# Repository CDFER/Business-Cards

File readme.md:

# PCB Business Cards

Welcome to my PCB business cards, a collection of functional devices showcasing my passion for embedded electronics and microcontrollers. Each card is a unique project demonstrating a specific concept or technology.

## USB Cable Tester MK2

* Simple, battery-powered USB 2.0 and 3.0 cable tester
* Protected by Schottky diodes and a polyfuse
* Indicates test results with LEDs

[Project Page](https://github.com/CDFER/Business-Cards/tree/main/USB_Cable_Tester_MK2)

## Tea Cozy Hotplate

* Temperature-controlled hotplate for perfect tea temperature
* Compact design, precise temperature control, and user-friendly interface

[Project Page](https://github.com/CDFER/Business-Cards/tree/main/Tea_Cozy_Hotplate)

## USB MicroPad

* 8-button macro pad for productivity shortcuts and macros
* Implemented as a USB HID keyboard and HID media consumer controller

[Project Page](https://github.com/CDFER/Business-Cards/tree/main/USB_Keypad)

## WLED Matrix

* 7x9 RGB matrix display powered by an ESP32C3 microcontroller
* Controlled from any web browser using WLED firmware

[Project Page](https://github.com/CDFER/Business-Cards/tree/main/WLED_Matrix)

## USB Cable Tester MK1

* Simple, battery-powered USB 2.0 and 3.0 cable tester
* Protected by Schottky diodes and a polyfuse
* Indicates test results with 0603 green LEDs

[Project Page](https://github.com/CDFER/Business-Cards/tree/main/USB_Cable_Tester)

### Support

Support my work by purchasing a custom CO2 sensor on my website or hiring me for freelance Embedded Electronics projects: [https://www.keastudios.co.nz](https://www.keastudios.co.nz/about.htm).

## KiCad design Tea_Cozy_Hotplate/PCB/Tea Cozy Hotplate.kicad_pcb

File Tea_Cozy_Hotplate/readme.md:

**Tea Cozy Hotplate**
=====================================

### Overview

The Tea Cozy Hotplate is a temperature-controlled hotplate designed to keep your cup of tea at the perfect temperature. It features a compact design, precise temperature control, and a user-friendly interface.

### Features

* Temperature control with ±2°C accuracy
* Compact design fits most tea cups
* User-friendly interface with addressable LED indicators
* Powered via USB-C connector (5V, 1.4A)
* STM32F103C8T6 microcontroller with 72MHz CPU

### Specifications

#### STM32 Specifications

* **CPU**: Arm Cortex-M3 @ 72MHz
* **Flash**: 64KB
* **RAM**: 20KB
* **Package**: LQFP-48

#### Components

* **Microcontroller**: STM32F103C8T6
* **LDO Regulator**: XC6206P332MR
* **ESD Protection**: SRV05
* **Fuse**: 2 x 1.5A Resettable Fuses
* **USB Connector**: USB-C Receptacle
* **Heating Element**: ~3.75Ω Spiral PCB Coil
* **Temperature Sensor**: 47kΩ NTC Thermistor

### Assembly and Programming

* Program the STM32 microcontroller using an ST-Link V2

### Issues with V1

* 3V3 LDO pinout incorrect

### Improvements for V2

* Reduce 3V3 LED brightness (half brightness)
* Use a cheaper USB-C connector
* Lower Resistance PCB Coil
* Consider Multi-Zone Heater
* Remove reset button?

## JLCPCB Heater Coil (1mm PCB with 1oz/ft^2)

* **Trace**: 2.8m length, 0.55mm width, 1oz/ft^2
* **Calculated Resistance**: 2.47Ω (assuming 0.000017Ω.mm)
* **Real-World Resistance**: 3.75Ω (calculated to be 0.0000258Ω.mm)

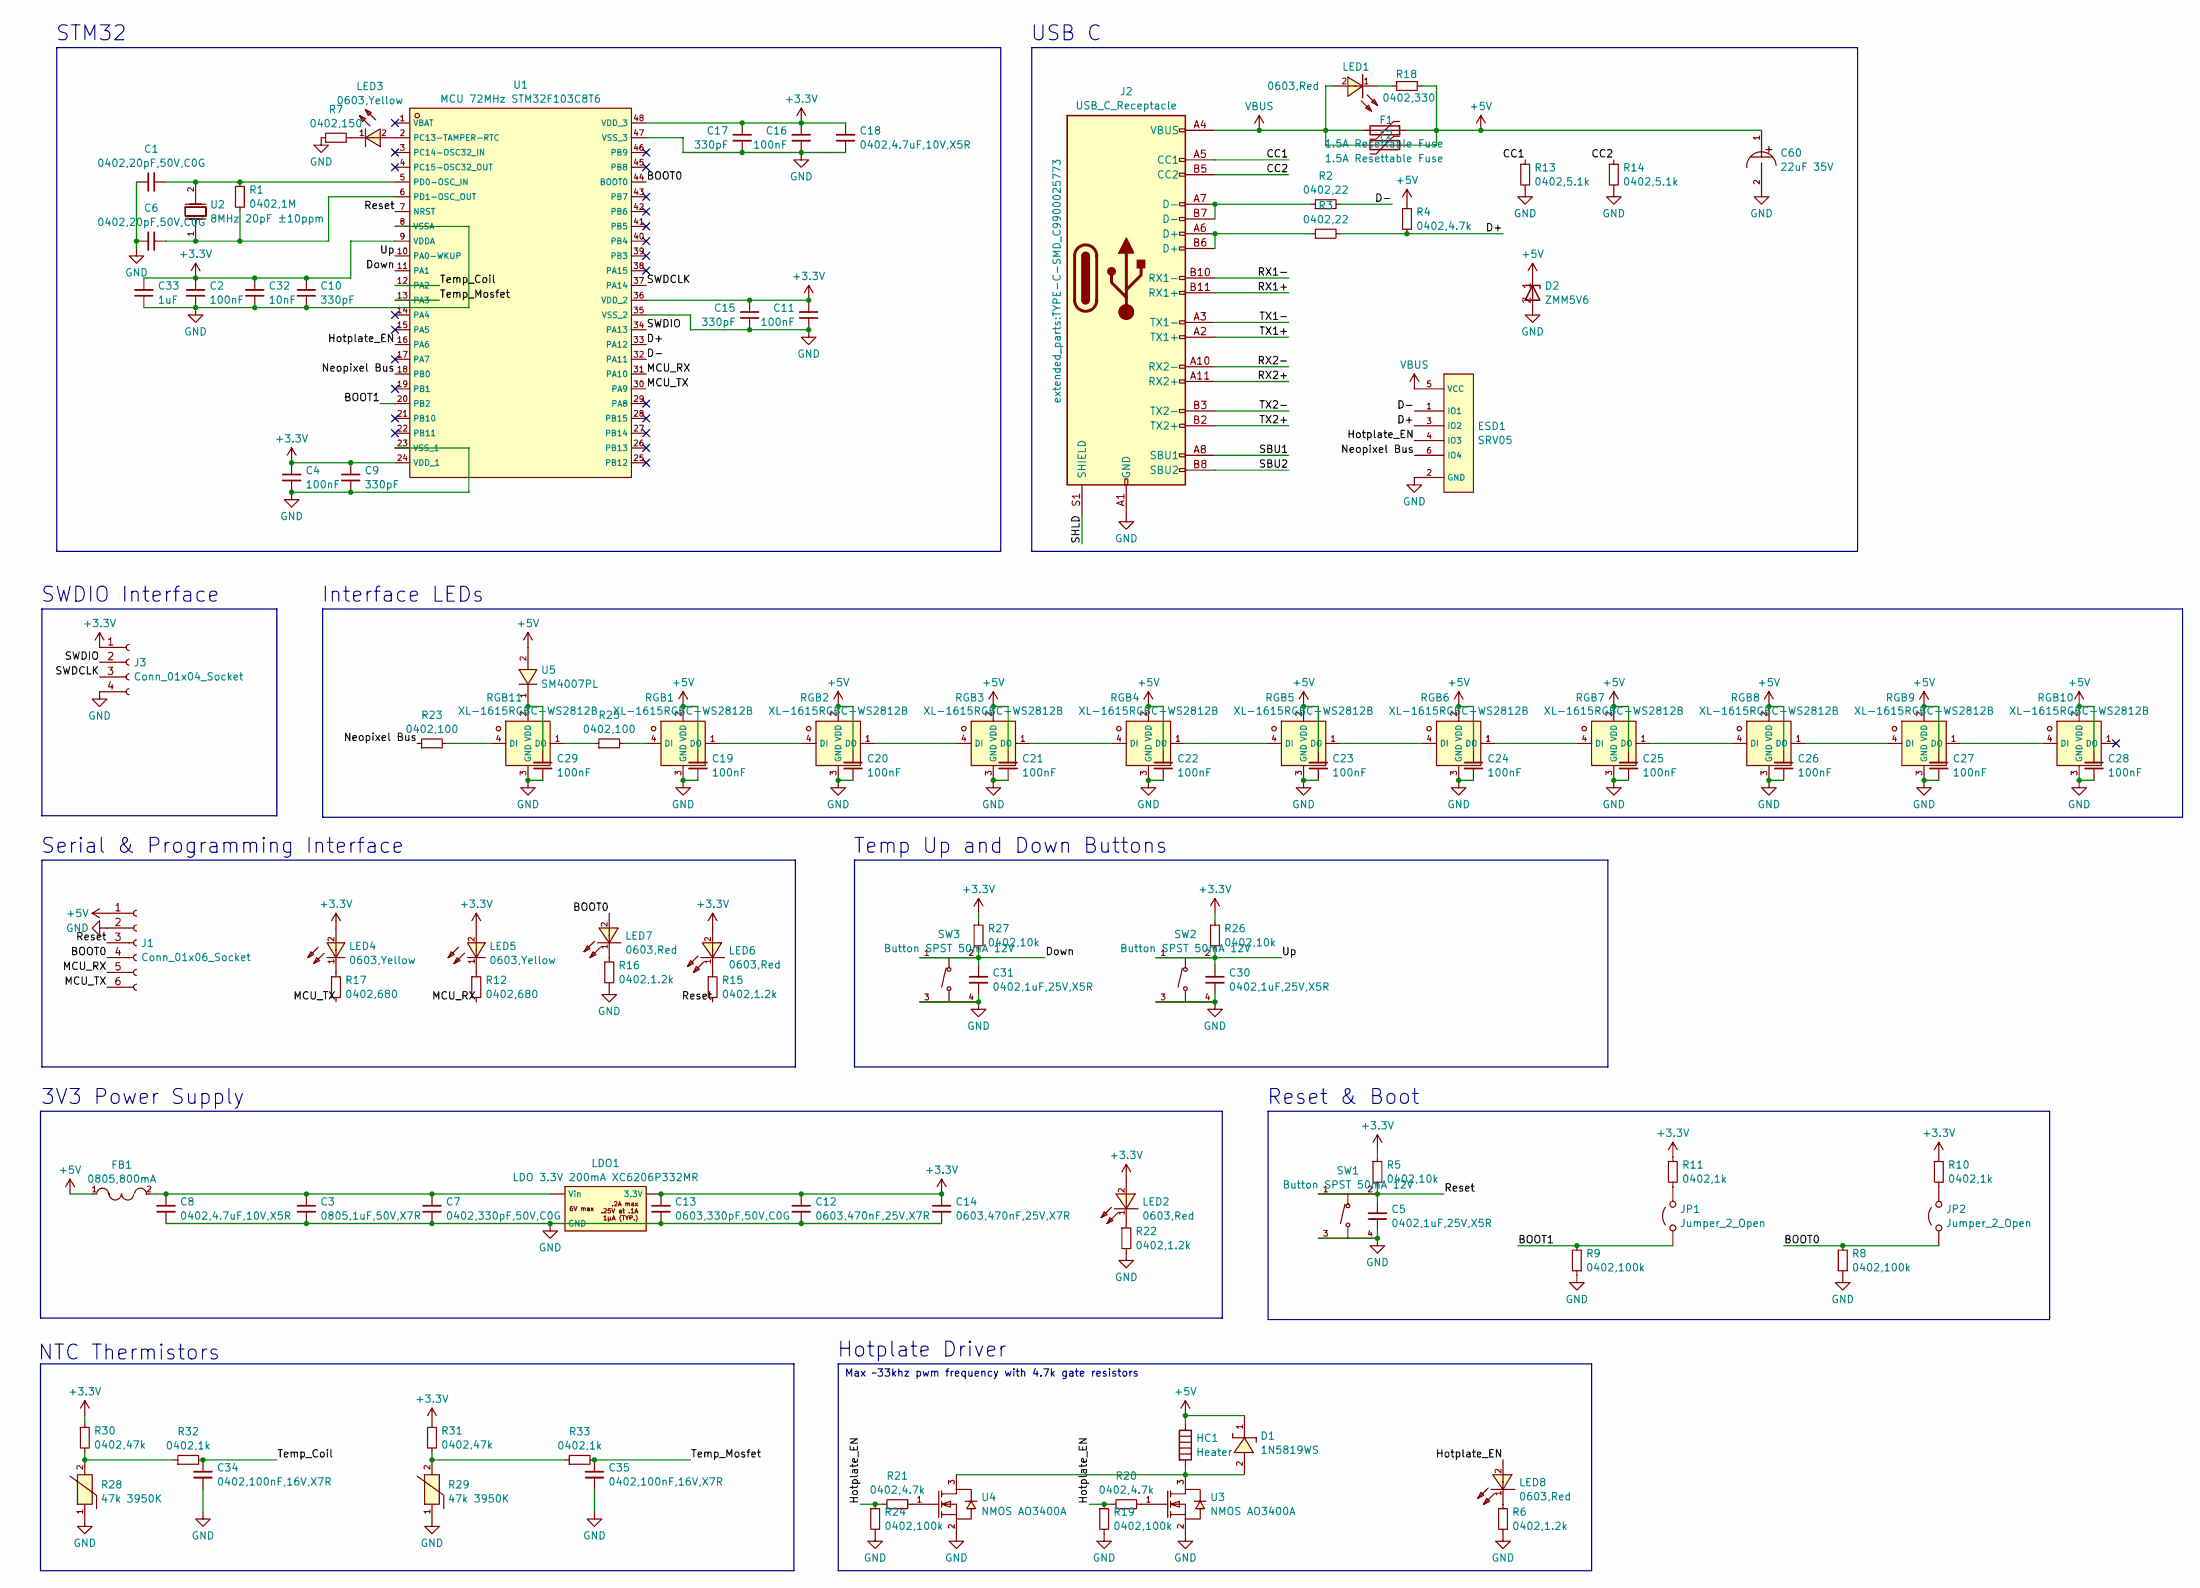
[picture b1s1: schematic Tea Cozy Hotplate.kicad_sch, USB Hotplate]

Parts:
C1, C6: 0402,20pF,50V,C0G; 0402_1005Metric; MFGPN 0402CG200J500NT; LCSC C1554
C2, C4, C11, C16, C19, C20, C21, C22, C23, C24, C25, C26, C27, C28, C29: 100nF; 0402_1005Metric; MFGPN CL05B104KO5NNNC; LCSC C1525
C3: 0805,1uF,50V,X7R; 0805_2012Metric; MFGPN CL21B105KBFNNNE; LCSC C28323
C5, C30, C31: 0402,1uF,25V,X5R; 0402_1005Metric; MFGPN CL05A105KA5NQNC; LCSC C52923
C7: 0402,330pF,50V,C0G; 0402_1005Metric; MFGPN CL05C331JB5NNNC; LCSC C13533
C8, C18: 0402,4.7uF,10V,X5R; 0402_1005Metric; MFGPN CL05A475MP5NRNC; LCSC C23733
C9, C10, C15, C17: 330pF; 0402_1005Metric; MFGPN CL05C331JB5NNNC; LCSC C13533
C12, C14: 0603,470nF,25V,X7R; 0603_1608Metric; MFGPN CL10B474KA8NNNC; LCSC C1623
C13: 0603,330pF,50V,C0G; 0603_1608Metric; MFGPN CL10C331JB8NNNC; LCSC C1664
C32: 10nF; 0402_1005Metric; MFGPN CL05B103KB5NNNC; LCSC C15195
C33: 1uF; 0805_2012Metric; MFGPN CL21B105KBFNNNE; LCSC C28323
C34, C35: 0402,100nF,16V,X7R; 0402_1005Metric; MFGPN CL05B104KO5NNNC; LCSC C1525
C60: 22uF 35V; CAP-SMD_BD5.0-L5.3-W5.3-LS6.0-FD; LCSC C2887274
D1: 1N5819WS; SOD-323_L1.8-W1.3-LS2.5-RD; LCSC C191023
D2: ZMM5V6; LL-34_L3.5-W1.5-RD; LCSC C8062
ESD1: SRV05; SOT-23-6_L2.9-W1.6-P0.95-LS2.8-BR; LCSC C85364
F1, F2: 1.5A Resettable Fuse; Fuse_1206_3216Metric; LCSC C2838983
FB1: 0805,800mA; 0805_2012Metric; LCSC C1015
HC1: Heater; heater_coil
J1: Conn_01x06_Socket; PinHeader_1x06_P2.54mm_Vertical
J2: USB_C_Receptacle; TYPE-C-SMD_C9900025773; LCSC C5156605
J3: Conn_01x04_Socket; PinHeader_1x04_P2.54mm_Vertical
JP1, JP2: Jumper_2_Open; SolderJumper-2_P1.3mm_Open_RoundedPad1.0x1.5mm
LDO1: LDO 3.3V 200mA XC6206P332MR; SOT-23-3_L2.9-W1.6-P1.90-LS2.8-BR; LCSC C5446
LED1, LED2, LED6, LED7, LED8: 0603,Red; LED0603; LCSC C2286
LED3, LED4, LED5: 0603,Yellow; LED0603; LCSC C72038
R1: 0402,1M; 0402_1005Metric; MFGPN 0402WGF1004TCE; LCSC C26083
R2, R3: 0402,22; 0402_1005Metric; MFGPN 0402WGF220JTCE; LCSC C25092
R4, R20, R21: 0402,4.7k; 0402_1005Metric; MFGPN 0402WGF4701TCE; LCSC C25900
R5, R26, R27: 0402,10k; 0402_1005Metric; MFGPN 0402WGF1002TCE; LCSC C25744
R6, R15, R16, R22: 0402,1.2k; 0402_1005Metric; MFGPN 0402WGF1201TCE; LCSC C25862
R7: 0402,150; 0402_1005Metric; MFGPN 0402WGF1500TCE; LCSC C25082
R8, R9, R19, R24: 0402,100k; 0402_1005Metric; MFGPN 0402WGF1003TCE; LCSC C25741
R10, R11, R32, R33: 0402,1k; 0402_1005Metric; MFGPN 0402WGF1001TCE; LCSC C11702
R12, R17: 0402,680; 0402_1005Metric; MFGPN 0402WGF6800TCE; LCSC C25130
R13, R14: 0402,5.1k; 0402_1005Metric; MFGPN 0402WGF5101TCE; LCSC C25905
R18: 0402,330; 0402_1005Metric; MFGPN 0402WGF3300TCE; LCSC C25104
R23, R25: 0402,100; 0402_1005Metric; MFGPN 0402WGF1000TCE; LCSC C25076
R28, R29: 47k 3950K; R0402; LCSC C2991699
R30, R31: 0402,47k; 0402_1005Metric; MFGPN 0402WGF4702TCE; LCSC C25792
RGB1, RGB2, RGB3, RGB4, RGB5, RGB6, RGB7, RGB8, RGB9, RGB10, RGB11: XL-1615RGBC-WS2812B; LED-SMD_4P-L1.6-W1.5_XL-1615RGBC-WS2812B; LCSC C5349954
SW1, SW2, SW3: Button SPST 50mA 12V; SW-SMD_4P-L5.1-W5.1-P3.70-LS6.5-TL-2; LCSC C318884
U1: MCU 72MHz STM32F103C8T6; LQFP-48_L7.0-W7.0-P0.50-LS9.0-BL; LCSC C8734
U2: 8MHz 20pF ±10ppm; CRYSTAL-SMD_L5.0-W3.2; LCSC C115962
U3, U4: NMOS AO3400A; SOT-23-3_L2.9-W1.6-P1.90-LS2.8-BR; LCSC C20917
U5: SM4007PL; SOD-123F_L2.8-W1.8-LS3.7-RD; LCSC C64898

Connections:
+3.3V: C2.1, C4.1, C9.1, C10.1, C11.1, C12.1, C13.1, C14.1, C15.1, C16.1, C17.1, C18.1, C32.1, C33.1, J3.1, LDO1.3 (3.3V), LED2.2 (A), LED4.2 (A), LED5.2 (A), LED6.2 (A), R5.1, R10.1, R11.1, R26.1, R27.1, R30.1, R31.1, U1.9 (VDDA), U1.24 (VDD_1), U1.36 (VDD_2), U1.48 (VDD_3)
+5V: C19.1, C20.1, C21.1, C22.1, C23.1, C24.1, C25.1, C26.1, C27.1, C28.1, C60.1, D1.1 (C), D2.1 (K), F1.1, F2.1, FB1.1, HC1.1, J1.1, R4.1, R18.1, RGB1.2 (VDD), RGB2.2 (VDD), RGB3.2 (VDD), RGB4.2 (VDD), RGB5.2 (VDD), RGB6.2 (VDD), RGB7.2 (VDD), RGB8.2 (VDD), RGB9.2 (VDD), RGB10.2 (VDD), U5.2 (A)
/BOOT0: J1.4, JP2.1 (A), LED7.2 (A), R8.2, U1.44 (BOOT0)
/BOOT1: JP1.1 (A), R9.2, U1.20 (PB2)
/CC1: J2.A5 (CC1), R13.1
/CC2: J2.B5 (CC2), R14.1
/D+: ESD1.3 (IO2), R3.2, R4.2, U1.33 (PA12)
/D-: ESD1.1 (IO1), R2.2, U1.32 (PA11)
/Down: C31.1, R27.2, SW3.1 (A), SW3.2 (B), U1.11 (PA1)
/Hotplate_EN: ESD1.4 (IO3), LED8.2 (A), R19.1, R20.1, R21.1, R24.1, U1.16 (PA6)
/MCU_RX: J1.5, R12.2, U1.31 (PA10)
/MCU_TX: J1.6, R17.2, U1.30 (PA9)
/Neopixel Bus: ESD1.6 (IO4), R23.1, U1.18 (PB0)
/RX1+: J2.B11 (RX1+)
/RX1-: J2.B10 (RX1-)
/RX2+: J2.A11 (RX2+)
/RX2-: J2.A10 (RX2-)
/Reset: C5.1, J1.3, R5.2, R15.2, SW1.1 (A), SW1.2 (B), U1.7 (NRST)
/SBU1: J2.A8 (SBU1)
/SBU2: J2.B8 (SBU2)
/SHLD: J2.S1 (SHIELD)
/SWDCLK: J3.3, U1.37 (PA14)
/SWDIO: J3.2, U1.34 (PA13)
/TX1+: J2.A2 (TX1+)
/TX1-: J2.A3 (TX1-)
/TX2+: J2.B2 (TX2+)
/TX2-: J2.B3 (TX2-)
/Temp_Coil: C34.1, R32.2, U1.12 (PA2)
/Temp_Mosfet: C35.1, R33.2, U1.13 (PA3)
/Up: C30.1, R26.2, SW2.1 (A), SW2.2 (B), U1.10 (PA0-WKUP)
GND: C1.1, C2.2, C3.2, C4.2, C5.2, C6.1, C7.2, C8.2, C9.2, C10.2, C11.2, C12.2, C13.2, C14.2, C15.2, C16.2, C17.2, C18.2, C19.2, C20.2, C21.2, C22.2, C23.2, C24.2, C25.2, C26.2, C27.2, C28.2, C29.2, C30.2, C31.2, C32.2, C33.2, C34.2, C35.2, C60.2, D2.2 (A), ESD1.2 (GND), J1.2, J2.A1 (GND), J2.A12 (GND), J2.B1 (GND), J2.B12 (GND), J3.4, LDO1.1 (GND), R6.2, R7.1, R8.1, R9.1, R13.2, R14.2, R16.2, R19.2, R22.2, R24.2, R28.1, R29.1, RGB1.3 (GND), RGB2.3 (GND), RGB3.3 (GND), RGB4.3 (GND), RGB5.3 (GND), RGB6.3 (GND), RGB7.3 (GND), RGB8.3 (GND), RGB9.3 (GND), RGB10.3 (GND), RGB11.3 (GND), SW1.3 (C), SW1.4 (D), SW2.3 (C), SW2.4 (D), SW3.3 (C), SW3.4 (D), U1.8 (VSSA), U1.23 (VSS_1), U1.35 (VSS_2), U1.47 (VSS_3), U3.2 (S), U4.2 (S)
unnamed: D1.2 (A), HC1.2, U3.3 (D), U4.3 (D)
unnamed: J2.A6 (D+), J2.B6 (D+), R3.1
unnamed: J2.A7 (D-), J2.B7 (D-), R2.1
unnamed: JP1.2 (B), R11.2
unnamed: JP2.2 (B), R10.2
unnamed: C3.1, C7.1, C8.1, FB1.2, LDO1.2 (Vin)
unnamed: LED1.1 (K), R18.2
unnamed: LED2.1 (K), R22.1
unnamed: LED3.2 (A), U1.2 (PC13-TAMPER-RTC)
unnamed: LED3.1 (C), R7.2
unnamed: LED4.1 (C), R17.1
unnamed: LED5.1 (C), R12.1
unnamed: LED6.1 (K), R15.1
unnamed: LED7.1 (K), R16.1
unnamed: LED8.1 (K), R6.1
unnamed: R28.2, R30.2, R32.1
unnamed: R29.2, R31.2, R33.1
unnamed: R25.2, RGB1.4 (DI)
unnamed: RGB1.1 (DO), RGB2.4 (DI)
unnamed: RGB2.1 (DO), RGB3.4 (DI)
unnamed: RGB3.1 (DO), RGB4.4 (DI)
unnamed: RGB4.1 (DO), RGB5.4 (DI)
unnamed: RGB5.1 (DO), RGB6.4 (DI)
unnamed: RGB6.1 (DO), RGB7.4 (DI)
unnamed: RGB7.1 (DO), RGB8.4 (DI)
unnamed: RGB8.1 (DO), RGB9.4 (DI)
unnamed: RGB9.1 (DO), RGB10.4 (DI)
unnamed: R23.2, RGB11.4 (DI)
unnamed: R25.1, RGB11.1 (DO)
unnamed: C29.1, RGB11.2 (VDD), U5.1 (C)
unnamed: C1.2, R1.1, U1.5 (PD0-OSC_IN), U2.2 (OSC2)
unnamed: C6.2, R1.2, U1.6 (PD1-OSC_OUT), U2.1 (OSC1)
unnamed: R20.2, U3.1 (G)
unnamed: R21.2, U4.1 (G)
VBUS: ESD1.5 (VCC), F1.2, F2.2, J2.A4 (VBUS), J2.A9 (VBUS), J2.B4 (VBUS), J2.B9 (VBUS), LED1.2 (A)

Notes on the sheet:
3V3 Power Supply
USB C
NTC Thermistors
Serial & Programming Interface
SWDIO Interface
Hotplate Driver
Interface LEDs
Max ~33khz pwm frequency with 4.7k gate resistors
STM32
Reset & Boot
Temp Up and Down Buttons

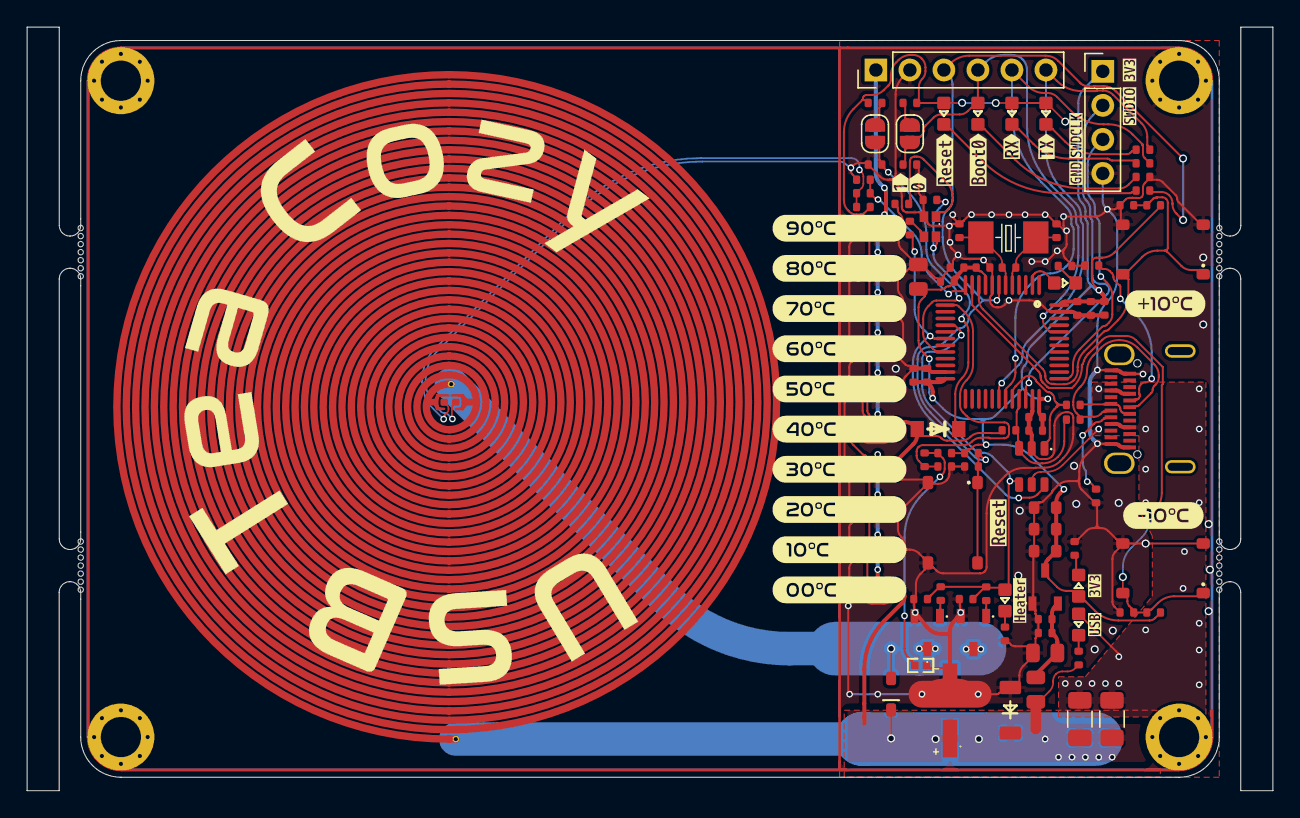
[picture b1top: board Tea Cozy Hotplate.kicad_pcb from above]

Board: 2 copper layers, 93.0 x 57.0 mm, 127 parts (0 on the bottom side), 55 nets.

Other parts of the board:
M1, M2, M3, M4: MountingHole_3.2mm_M3
kibuzzard-669770AA: G***; kibuzzard-669770AA
kibuzzard-669770B6: G***; kibuzzard-669770B6
kibuzzard-669770CC: G***; kibuzzard-669770CC
kibuzzard-669770DC: G***; kibuzzard-669770DC
kibuzzard-669771D1: G***; kibuzzard-669771D1
kibuzzard-669771DB: G***; kibuzzard-669771DB
kibuzzard-6697705A: G***; kibuzzard-6697705A
kibuzzard-6697709F: G***; kibuzzard-6697709F
kibuzzard-6697716D: G***; kibuzzard-6697716D
kibuzzard-6697719B: G***; kibuzzard-6697719B
kibuzzard-66977083: G***; kibuzzard-66977083
kibuzzard-66977187: G***; kibuzzard-66977187
kibuzzard-66977193: G***; kibuzzard-66977193
kibuzzard-66977218: G***; kibuzzard-66977218

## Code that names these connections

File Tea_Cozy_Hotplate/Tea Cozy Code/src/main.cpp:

#include <Arduino.h>
#include <Adafruit_NeoPixel.h>
// Change on line 2862 of Adafruit_NeoPixel.cpp
// uint32_t top = 90;  // 1.25µs
// uint32_t t0 = 79;   // 0.4µs was 62 (62-79)
// uint32_t t1 = 30;   // 0.8µs was 33

const int upButton = PA0;
const int downButton = PA1;
const int tempCoil = PA2;
const int tempMosfet = PA3;
const int neopixelBus = PB0;
const int hotplateGate = PA6;
const int debugLED = PC13;

const unsigned long debounceTime = 250;  // Debounce time in milliseconds

#define NUM_PIXELS 11
#define BRIGHTNESS 16

Adafruit_NeoPixel pixels(NUM_PIXELS, neopixelBus, NEO_GRB + NEO_KHZ800);


float coilTemp = 0;
float mosfetTemp = 0;
float targetTemp = 60.0;

volatile bool upButtonState = false;
volatile bool downButtonState = false;
volatile unsigned long upButtonLastPress = 0;
volatile unsigned long downButtonLastPress = 0;

float readThermistorTemperature(uint32_t thermistorPin) {
    int analogValue = analogRead(thermistorPin);
    float voltage = analogValue * 3.3 / 4095;
    float resistance = voltage * 47000 / (3.3 - voltage);  // Calculate thermistor resistance
    float temperature = 1 / (log(resistance / 47000) / 3950 + 1 / 298.15) - 273.15;
    return temperature;
}

uint32_t black = pixels.Color(0, 0, 0);
uint32_t green = pixels.Color(0, BRIGHTNESS, 0);
uint32_t red = pixels.Color(BRIGHTNESS, 0, 0);
uint32_t endGreen;

void drawTemp(float degC) {
    uint16_t intPosition = (degC / 90) * (10 * BRIGHTNESS);

    pixels.setPixelColor(0, black);

    for (uint16_t i = NUM_PIXELS - 1; i > 0; i--) {
        if (intPosition >= BRIGHTNESS) {
            pixels.setPixelColor(i, green);
            intPosition -= BRIGHTNESS;
        } else if (intPosition > 0) {
            endGreen = pixels.Color(0, intPosition, 0);
            pixels.setPixelColor(i, endGreen);
            intPosition = 0;
        } else {
            pixels.setPixelColor(i, black);
        }
    }
    pixels.show();
}

void drawTargetTemp(float degC) {
    uint16_t intPosition = NUM_PIXELS - ((degC / 90) * (NUM_PIXELS-1));

    pixels.clear();
    pixels.setPixelColor(intPosition, red);
    pixels.show();
}

enum ledStates : uint8_t { STARTUP,
                           TEMP,
                           TARGET,
                           TEMP_TO_TARGET,
                           TARGET_TO_TEMP };

ledStates ledState = STARTUP;
uint8_t stateCounter;

void updateLEDs() {
    switch (ledState) {
        case STARTUP:
            pixels.begin();
            pixels.clear();
            pixels.show();
            ledState = TEMP;
            break;

        case TEMP:
            drawTemp(coilTemp);
            break;

        case TARGET:
            drawTargetTemp(targetTemp);
            stateCounter++;
            if (stateCounter >= 100) {
                ledState = TARGET_TO_TEMP;
            }
            break;

        case TEMP_TO_TARGET:
            stateCounter = 0;
            ledState = TARGET;
            break;

        case TARGET_TO_TEMP:
            ledState = TEMP;
            break;

        default:
            break;
    }
}

void upButtonPressHandler() {
    unsigned long currentTime = millis();
    if (currentTime - upButtonLastPress > debounceTime) {
        upButtonState = true;
        upButtonLastPress = currentTime;
    }
}

void downButtonPressHandler() {
    unsigned long currentTime = millis();
    if (currentTime - downButtonLastPress > debounceTime) {
        downButtonState = true;
        downButtonLastPress = currentTime;
    }
}

void setup() {
    pinMode(debugLED, OUTPUT);
    pinMode(upButton, INPUT);
    pinMode(downButton, INPUT);
    pinMode(tempMosfet, INPUT);
    pinMode(tempCoil, INPUT);
    pinMode(hotplateGate, OUTPUT);
    pinMode(neopixelBus, OUTPUT);

    analogReadResolution(12);

    attachInterrupt(upButton, upButtonPressHandler, RISING);
    attachInterrupt(downButton, downButtonPressHandler, RISING);
}


void loop() {
    if (upButtonState || downButtonState) {
        if (upButtonState && targetTemp < 90.0) {
            targetTemp += 10.0;
        }

        if (downButtonState && targetTemp > 10.0) {
            targetTemp -= 10.0;
        }

        ledState = TEMP_TO_TARGET;
        upButtonState = false;
        downButtonState = false;
    }

    coilTemp = (coilTemp * 0.9) + (0.1 * readThermistorTemperature(tempCoil));
    mosfetTemp = readThermistorTemperature(tempMosfet);

    if (coilTemp < targetTemp && mosfetTemp < 50) {
        digitalWrite(hotplateGate, HIGH);
    } else {
        digitalWrite(hotplateGate, LOW);
    }

    if (mosfetTemp > 50) {
        digitalWrite(debugLED, HIGH);
    } else {
        digitalWrite(debugLED, LOW);
    }

    delay(10);  //for some reason leds can only be updated every 256ms otherwise timing is way off.
    updateLEDs();
}

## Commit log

2024-07-08 add gitignore
2024-07-09 USB Cable Tester V1
2024-08-12 Batch 1 (First 4) Business Cards
2024-08-12 Fix readme.md likns
2024-09-01 update USB Cable Tester Readme
2024-09-01 add schematic svg files to readme of each project
2024-09-02 update main readme with link text
2024-09-22 initial linear motor commit
2024-09-25 USB Cable Tester PCB Design
2024-10-07 add documentation
